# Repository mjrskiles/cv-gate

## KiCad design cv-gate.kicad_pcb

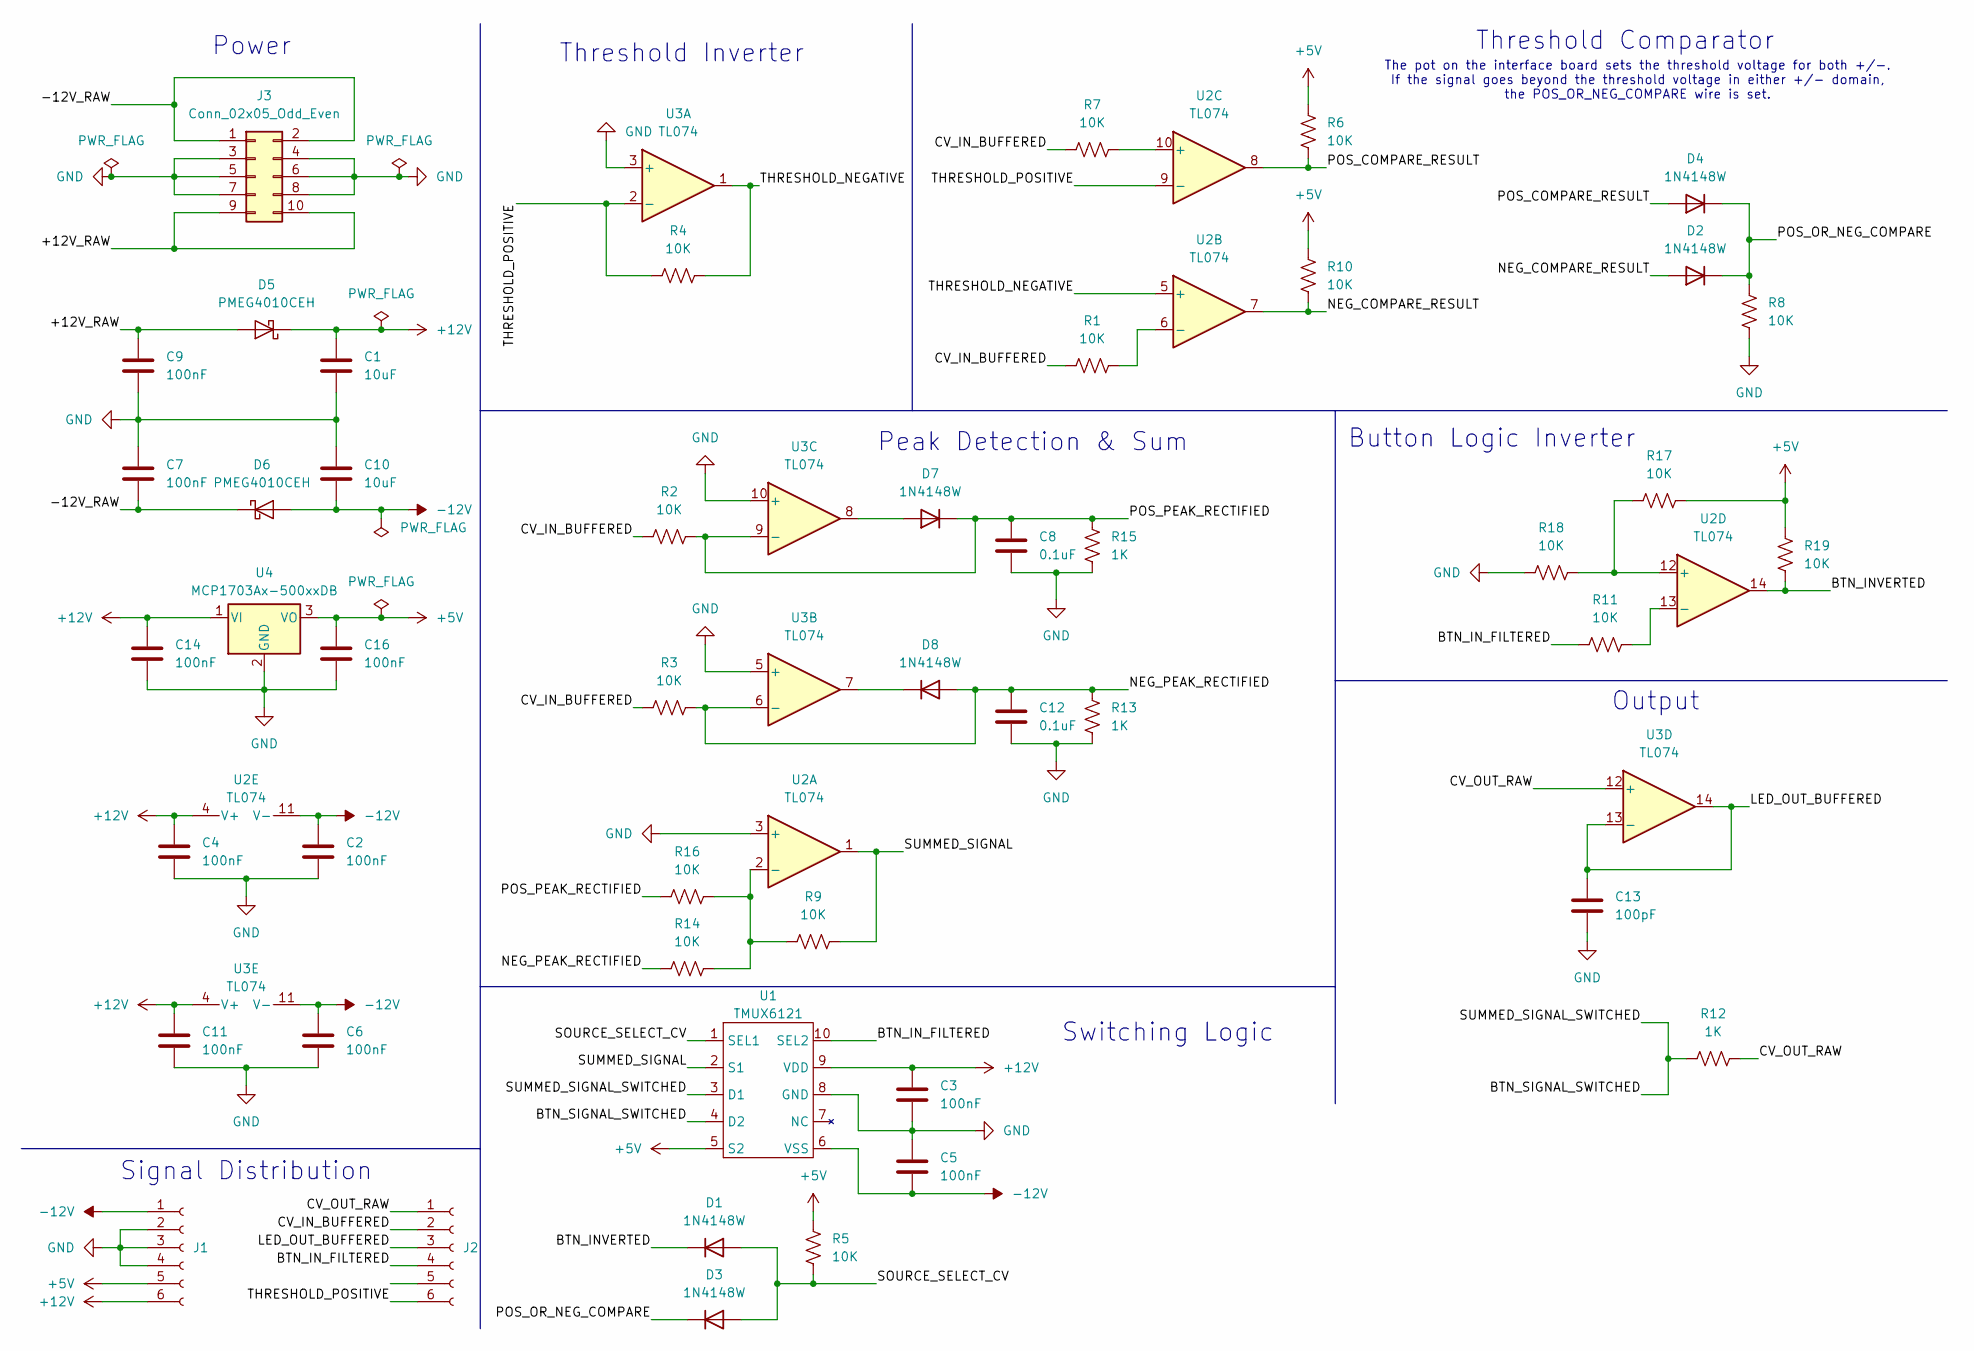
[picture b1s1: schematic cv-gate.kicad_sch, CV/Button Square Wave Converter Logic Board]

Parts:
C1, C10: 10uF; C_0805_2012Metric_Pad1.18x1.45mm_HandSolder
C2, C3, C4, C5, C6, C7, C9, C11, C14, C16: 100nF; C_0805_2012Metric_Pad1.18x1.45mm_HandSolder
C8, C12: 0.1uF; C_0805_2012Metric_Pad1.18x1.45mm_HandSolder
C13: 100pF; C_0805_2012Metric_Pad1.18x1.45mm_HandSolder
D1, D2, D3, D4, D7, D8: 1N4148W; D_SOD-123
D5, D6: PMEG4010CEH; D_SOD-123F
J1, J2: Conn_01x06_Socket; PinSocket_1x06_P1.27mm_Vertical
J3: Conn_02x05_Odd_Even; PinHeader_2x05_P2.54mm_Vertical
R1, R2, R3, R4, R5, R6, R7, R8, R9, R10, R11, R14, R16, R17, R18, R19: 10K; R_0805_2012Metric_Pad1.20x1.40mm_HandSolder
R12, R13, R15: 1K; R_0805_2012Metric_Pad1.20x1.40mm_HandSolder
U1: TMUX6121; VSSOP-10_3x3mm_P0.5mm
U2, U3: TL074; SOIC-14_3.9x8.7mm_P1.27mm
U4: MCP1703Ax-500xxDB; SOT-223-3_TabPin2

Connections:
+5V: C16.2, J1.5, R5.1, R6.1, R10.1, R17.2, R19.2, U1.5 (S2), U4.3 (VO)
+12V: C1.2, C3.2, C4.2, C11.2, C14.2, D5.1 (K), J1.6, U1.9 (VDD), U2.4 (V+), U3.4 (V+), U4.1 (VI)
-12V: C2.2, C5.1, C6.2, C10.1, D6.2 (A), J1.1, U1.6 (VSS), U2.11 (V-), U3.11 (V-)
/+12V_RAW: C9.2, D5.2 (A), J3.9, J3.10
/-12V_RAW: C7.1, D6.1 (K), J3.1, J3.2
/BTN_INVERTED: D1.1 (K), R19.1, U2.14
/BTN_IN_FILTERED: J2.4, R11.1, U1.10 (SEL2)
/BTN_SIGNAL_SWITCHED: R12.1, U1.3 (D1), U1.4 (D2)
/CV_IN_BUFFERED: J2.2, R1.2, R2.2, R3.2, R7.2
/CV_OUT_RAW: J2.1, R12.2, U3.12 (+)
/LED_OUT_BUFFERED: C13.2, J2.3, U3.13 (-), U3.14
/NEG_COMPARE_RESULT: D2.2 (A), R10.2, U2.7
/NEG_PEAK_RECTIFIED: C12.1, D8.2 (A), R3.1, R13.2, R14.1, U3.6 (-)
/POS_COMPARE_RESULT: D4.2 (A), R6.2, U2.8
/POS_OR_NEG_COMPARE: D2.1 (K), D3.1 (K), D4.1 (K), R8.1
/POS_PEAK_RECTIFIED: C8.1, D7.1 (K), R2.1, R15.2, R16.1, U3.9 (-)
/SOURCE_SELECT_CV: D1.2 (A), D3.2 (A), R5.2, U1.1 (SEL1)
/SUMMED_SIGNAL: R9.2, U1.2 (S1), U2.1
/THRESHOLD_NEGATIVE: R4.1, U2.5 (+), U3.1
/THRESHOLD_POSITIVE: J2.6, R4.2, U2.9 (-), U3.2 (-)
GND: C1.1, C2.1, C3.1, C4.1, C5.2, C6.1, C7.2, C8.2, C9.1, C10.2, C11.1, C12.2, C13.1, C14.1, C16.1, J1.2, J1.3, J1.4, J3.3, J3.4, J3.5, J3.6, J3.7, J3.8, R8.2, R13.1, R15.1, R18.1, U1.8 (GND), U2.3 (+), U3.3 (+), U3.5 (+), U3.10 (+), U4.2 (GND)
unnamed: D7.2 (A), U3.8
unnamed: D8.1 (K), U3.7
unnamed: R9.1, R14.2, R16.2, U2.2 (-)
unnamed: R1.1, U2.6 (-)
unnamed: R7.1, U2.10 (+)
unnamed: R17.1, R18.2, U2.12 (+)
unnamed: R11.2, U2.13 (-)

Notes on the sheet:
The pot on the interface board sets the threshold voltage for both +/-. If the signal goes beyond the threshold voltage in either +/- domain, the POS_OR_NEG_COMPARE wire is set.
Switching Logic
Threshold Inverter
Signal Distribution
Button Logic Inverter
Peak Detection & Sum
Threshold Comparator
Power
Output

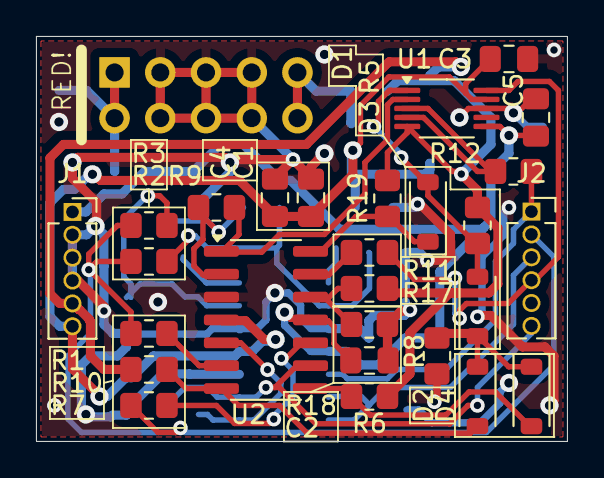
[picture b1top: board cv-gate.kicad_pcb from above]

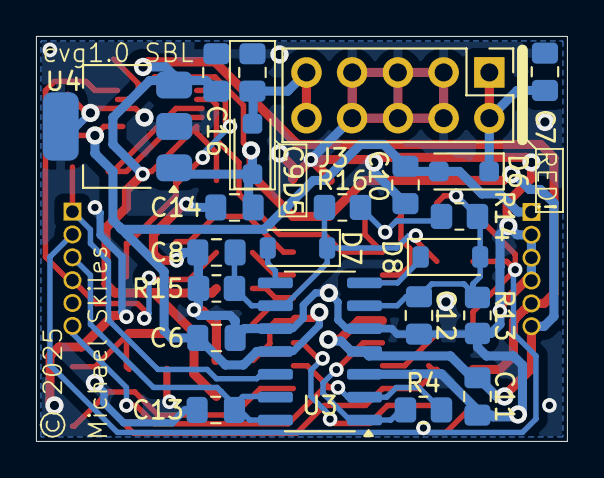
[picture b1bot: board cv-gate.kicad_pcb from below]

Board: 2 copper layers, 29.5 x 22.5 mm, 49 parts (22 on the bottom side), 28 nets.

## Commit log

2025-03-08 Moved I/O buffering to interface board, add license
2025-03-08 Update index.md with link to github repo
2025-03-12 Add bom, 3d model

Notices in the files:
cv-gate.kicad_pcb:
© 2025
